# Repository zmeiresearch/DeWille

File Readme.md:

# DeWille - A modular Audio DAC platform

DeWille is designed to be a set of building blocks for audio DACs. Currently, the following 'blocks' are planned:
* A Base board - Power supplies, interconnects, physical board support
* A Control board - Input selection, reclocking, other digital signal processing
* A PCM1792 DAC board
* An I/V converter board

## Features:
### Inputs/Outputs and interface
* Supports multiple input and output formats:
  * I2S, Left-justified and right-justified PCM
  * S/PDIF, optical and coaxial
  * (Maybe) DSD
* Supports at least 24-bit@192kHz
* Configurable asynchronous reclocking with a FIFO
* Provision for USB support based on either XMOS or Amanero COTS board 
* Provision for Bluetooth audio support
* Provision for playback via WiFi
* Provision for an (oled?) display

### Analog side
* DAC section based on PCM1792
* Supports DAC Mono mode
* Supports PCM1792(4) in NOS mode (inspired by DDAC)
* CCS for PCM1792 Iref
* Supports multiple I/V Converters
* Low-noise power supply for both analog and digital sections

## Design considerations

### Control board
The control board is by far the most complex one in the set. It implements input selection, reclocking as well as all
the signal conversion and processing required to drive the DACs. Several distinct components work together to do this 
- an FPGA, a clock generator block and an MCU module. All the blocks are connected to each other via an SPI bus, with 
the MCU acting as master. The SPI bus also connects to the two DAC boards, allowing on-the-fly reconfiguration as 
required.

#### Hardware Design
* **FPGA**
The FPGA is the one actually doing all the signal manipulation and transformation work. It takes I2S data (PCM and DSD
planned for the future), does the actual reclocking (if told to do so) and outputs I2S (DSD planned for the future) to
the two separate DAC board.

The choice of an FPGA has been a difficult one. First and foremost, an SMD(QFP) package is a must. I have no problem
hand-soldering 0402 components, but I have neither the equipment nor the expertise to handle BGAs reliably. This 
alone limits the choice to basically Xilinx Spartan 3 and some Lattice families. (Intel and Microchip not considered
for different reasons). With ISE 14.7 the last one supporting Spartan 3 and the family NRND for new designs in general
I settled on Lattice, LFXP2-8E-5TN144 in particular. MachXO2 is also an option for a future redesign.

There is an on-board 8-bit wide SRAM chip, with a maximal capacity of 8MBit. Possiblity for a future update is either 
increasing the SRAM size (larger buffer) or increasing the datapath width (better throughput/lower latency).

The FPGA can also be programmed and debugged using the integrated FT2232 interface or the standard Lattice JTAG
connector. If using the FT2232, the second channel is connected to two FPGA pins that could implement a debug UART.

* **Clock generator**
The clock generator block is implemented with two oscillators (at 24.576MHz and 22.5792MHz) and an Si5344 multiplexer,
jitter reduction and clock output buffer circuit. Two of the clock outputs go directly to the DAC boards via either 
the pin header or a dedicated SMA interconnect, while the third is distributed to the FPGA to drive the reclocking 
internally. This clock arrangement is guaranteed to introduce a phase margin between the master clock and the bit/data
clock, but the PCM1794(2) and, in theory, all other DACs that require a System/Master clock do not need a specific 
relation between the two, as long as it remains a fixed one.
Regular oscillators are used rather than TCXOs because the actual frequency and long term drift are not that important 
to the sound quality and the Si5344 performance dominates the short-term jitter performance 

Possibility for a future enchancement is to also route the SCK input from the two I2S inputs to the remaining two
Si5344 inputs to allow source-synchronous operation as well.

* **MCU**
A ESP32-DevKit module was selected for the main MCU. The rationale to use an off-the-shelf MCU module is two-fold.
_First,_ by using an COTS hardware module with a well-established and easy to use software ecosystem behind it, I'll
be able to focus on the signal processing part of the project.
_Second,_ it will be much easier to implement other functionality in the future - OTA updates, including the FPGA 
bitstream, WiFi streaming, Alexa/Google home integration, etc.

* **Power Supply**
The control board takes a single, 5V regulated power supply. There is an on-board protection by means of a polyfuse
and a 6.8V Transil. This is powering a total of 6 voltage regulators:
  * +3V3_IO and +3V3_FPGA -  used for FPGA I/O ports, Debug/Program USB and on-board LEDs
  * +1V2_FPGA - FPGA Core supply
  * +3V3_CLKOUT - Clock outputs of Si5344
  * +3V3_VDDACLK and +1V8VDDCLK - analog and digital sections of Si5344 respectively
  * +3v3_VDDOSC - the two crystal oscillators
  * The on-module voltage regulator in the ESP32 module.

### DAC PCM1794(2)

### Base Board
The base board is responsible for physically carying the different modules together, connecting them electrically and
providing all the required power supplies. In addition, it implements input signal galvanic isolation to limit the harm
in case of failure of signal sources.

* **Power supply**
The base board takes a 220/110VAC mains supply and has two separate sets of transformers. Either 50VAC toroidal power
transformers or PCB-mounted sealed ones can be used. One of the transformers is providing the +5V regulated supply
necessary for the digital part of the schematic, while the other provides a +/- 15V supply.

All three +5V power supplies are filtered and regulated using a hybrid capacitance multiplier/regulator circut. In
addition, there are also two 3.3V regulators for the input galvanic isolators - an LDO for the 'in' side and a 
DC-DC for the 'out' side.

### I to V module
**WiP/TBD.** Assumed to have the same dimensions as the DAC module while creating the Base board.

## FAQ
* **Is DeWille HiFi/Audiophile grade?**
  No. It will just sound good.
* **Where does the name DeWille come from?**
  It was inspired by a [Frey Wille](https://www.freywille.com) scharf that happened to be around while thinking about
  a name for the project.

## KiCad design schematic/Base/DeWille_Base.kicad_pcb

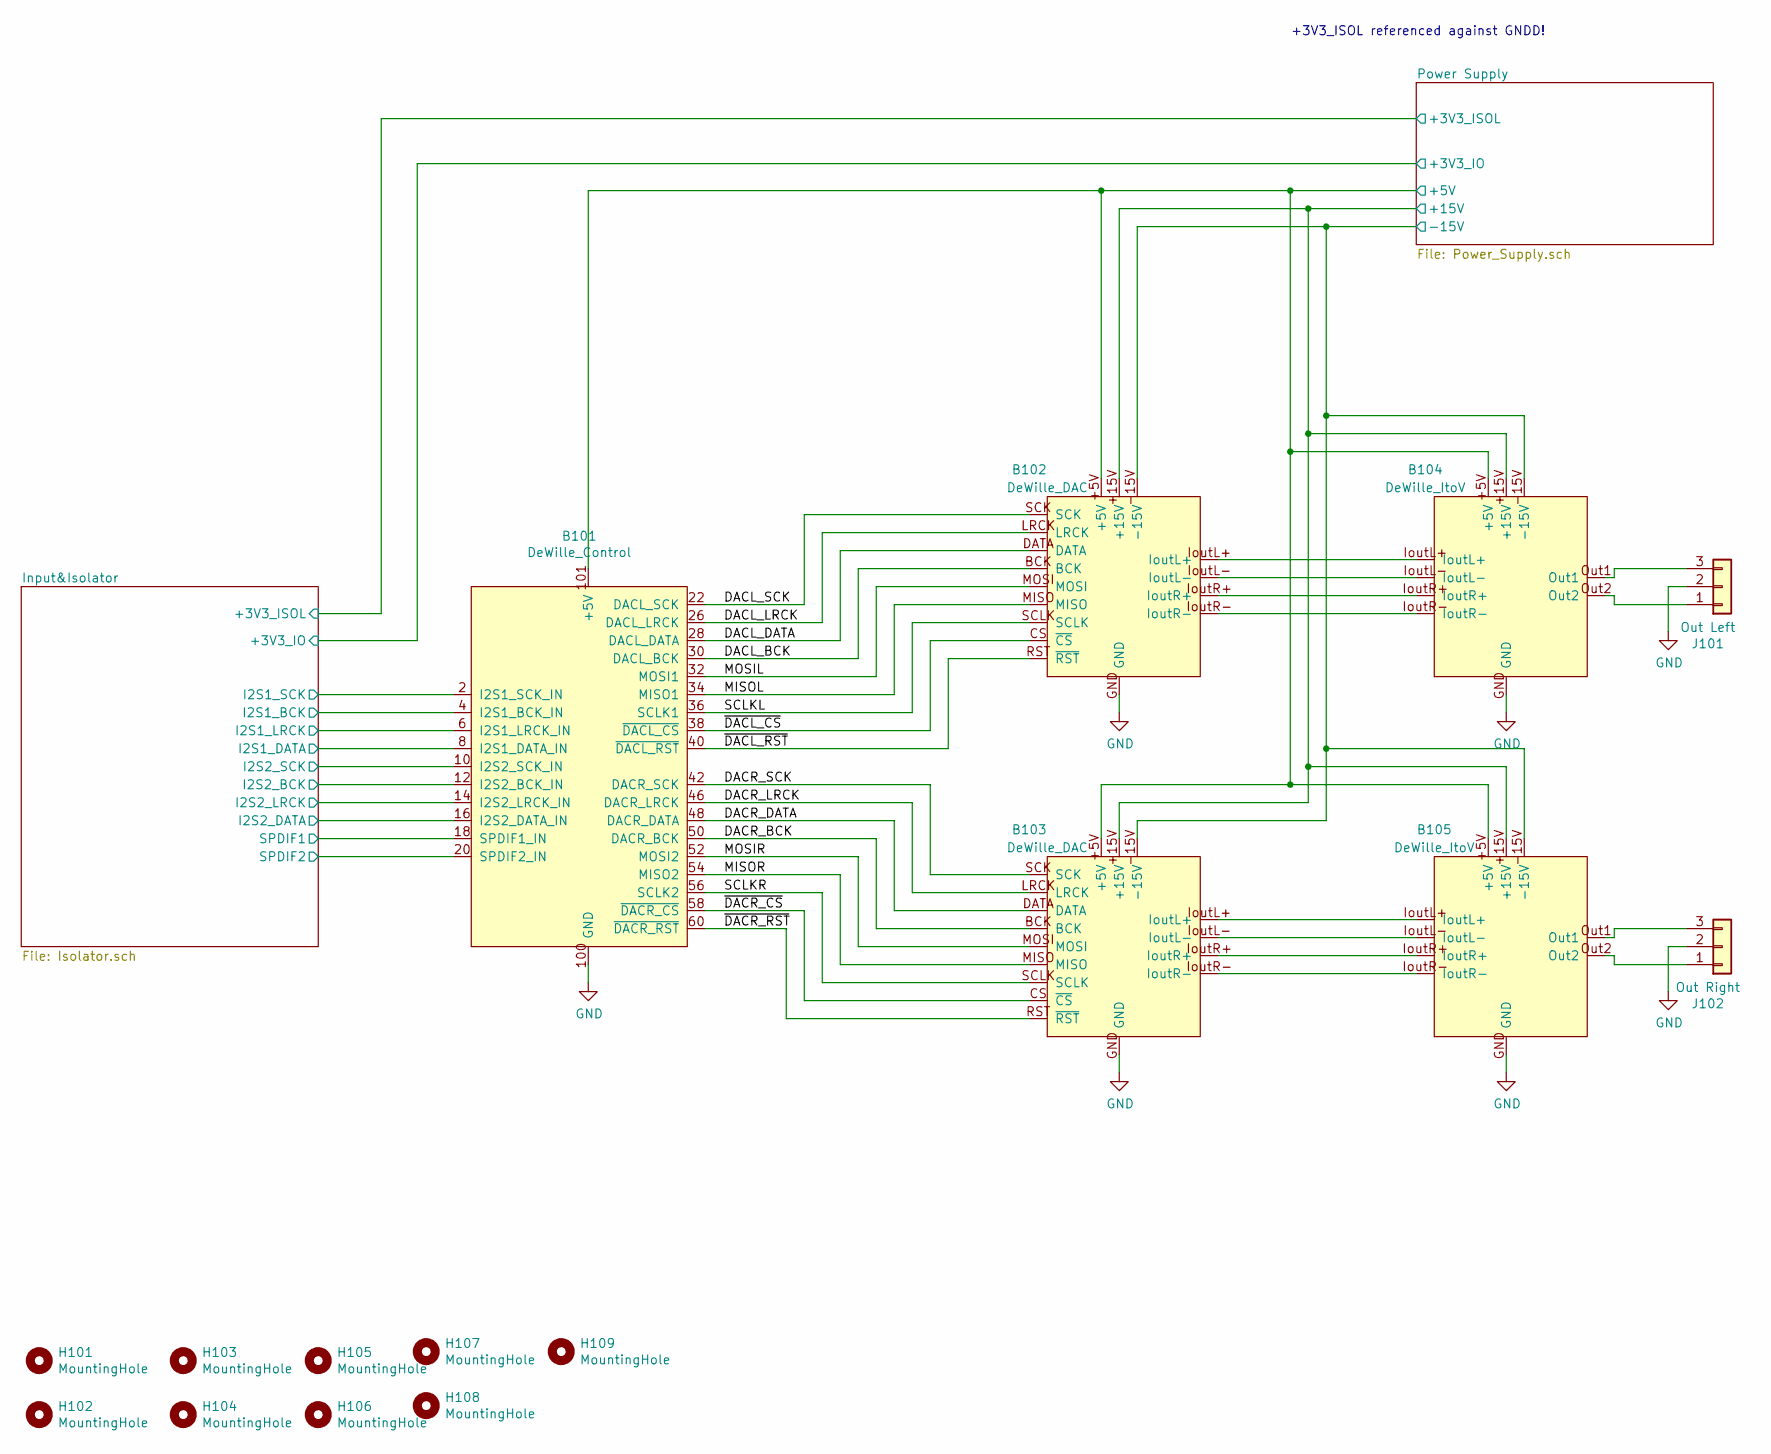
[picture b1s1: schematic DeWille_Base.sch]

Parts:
B101: DeWille_Control
B102, B103: DeWille_DAC
B104, B105: DeWille_ItoV
H101, H102, H103, H104, H105, H106, H107, H108, H109: MountingHole; MountingHole_3.2mm_M3_Pad
J101: Out Left; TerminalBlock_Dinkle_DT-55-B01X-03_P10.00mm
J102: Out Right; TerminalBlock_Dinkle_DT-55-B01X-03_P10.00mm

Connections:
/DACL_BCK: B101.30 (DACL_BCK), B102.BCK
/DACL_DATA: B101.28 (DACL_DATA), B102.DATA
/DACL_LRCK: B101.26 (DACL_LRCK), B102.LRCK
/DACL_SCK: B101.22 (DACL_SCK), B102.SCK
/DACR_BCK: B101.50 (DACR_BCK), B103.BCK
/DACR_DATA: B101.48 (DACR_DATA), B103.DATA
/DACR_LRCK: B101.46 (DACR_LRCK), B103.LRCK
/DACR_SCK: B101.42 (DACR_SCK), B103.SCK
/Input&Isolator/I2S1_BCK: B101.4 (I2S1_BCK_IN); also elsewhere on the board
/Input&Isolator/I2S1_DATA: B101.8 (I2S1_DATA_IN); also elsewhere on the board
/Input&Isolator/I2S1_LRCK: B101.6 (I2S1_LRCK_IN); also elsewhere on the board
/Input&Isolator/I2S1_SCK: B101.2 (I2S1_SCK_IN); also elsewhere on the board
/Input&Isolator/I2S2_BCK: B101.12 (I2S2_BCK_IN); also elsewhere on the board
/Input&Isolator/I2S2_DATA: B101.16 (I2S2_DATA_IN); also elsewhere on the board
/Input&Isolator/I2S2_LRCK: B101.14 (I2S2_LRCK_IN); also elsewhere on the board
/Input&Isolator/I2S2_SCK: B101.10 (I2S2_SCK_IN); also elsewhere on the board
/Input&Isolator/SPDIF1: B101.18 (SPDIF1_IN); also elsewhere on the board
/Input&Isolator/SPDIF2: B101.20 (SPDIF2_IN); also elsewhere on the board
/MISOL: B101.34 (MISO1), B102.MISO
/MISOR: B101.54 (MISO2), B103.MISO
/MOSIL: B101.32 (MOSI1), B102.MOSI
/MOSIR: B101.52 (MOSI2), B103.MOSI
/Power Supply/+5V: B101.101 (+5V), B102.+5V, B103.+5V, B104.+5V, B105.+5V; also elsewhere on the board
/Power Supply/+15V: B102.+15V, B103.+15V, B104.+15V, B105.+15V; also elsewhere on the board
/Power Supply/-15V: B102.-15V, B103.-15V, B104.-15V, B105.-15V; also elsewhere on the board
/SCLKL: B101.36 (SCLK1), B102.SCLK
/SCLKR: B101.56 (SCLK2), B103.SCLK
/~DACL_CS~: B101.38 (~DACL_CS~), B102.~CS~
/~DACL_RST~: B101.40 (~DACL_RST~), B102.~RST~
/~DACR_CS~: B101.58 (~DACR_CS~), B103.~CS~
/~DACR_RST~: B101.60 (~DACR_RST~), B103.~RST~
GND: B101.100 (GND), B102.GND, B103.GND, B104.GND, B105.GND, J101.2, J102.2; also elsewhere on the board
unnamed: B102.IoutL+, B104.IoutL+
unnamed: B102.IoutL-, B104.IoutL-
unnamed: B102.IoutR+, B104.IoutR+
unnamed: B102.IoutR-, B104.IoutR-
unnamed: B103.IoutL+, B105.IoutL+
unnamed: B103.IoutL-, B105.IoutL-
unnamed: B103.IoutR+, B105.IoutR+
unnamed: B103.IoutR-, B105.IoutR-
unnamed: B104.Out1, J101.3
unnamed: B104.Out2, J101.1
unnamed: B105.Out1, J102.3
unnamed: B105.Out2, J102.1

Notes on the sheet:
+3V3_ISOL referenced against GNDD!

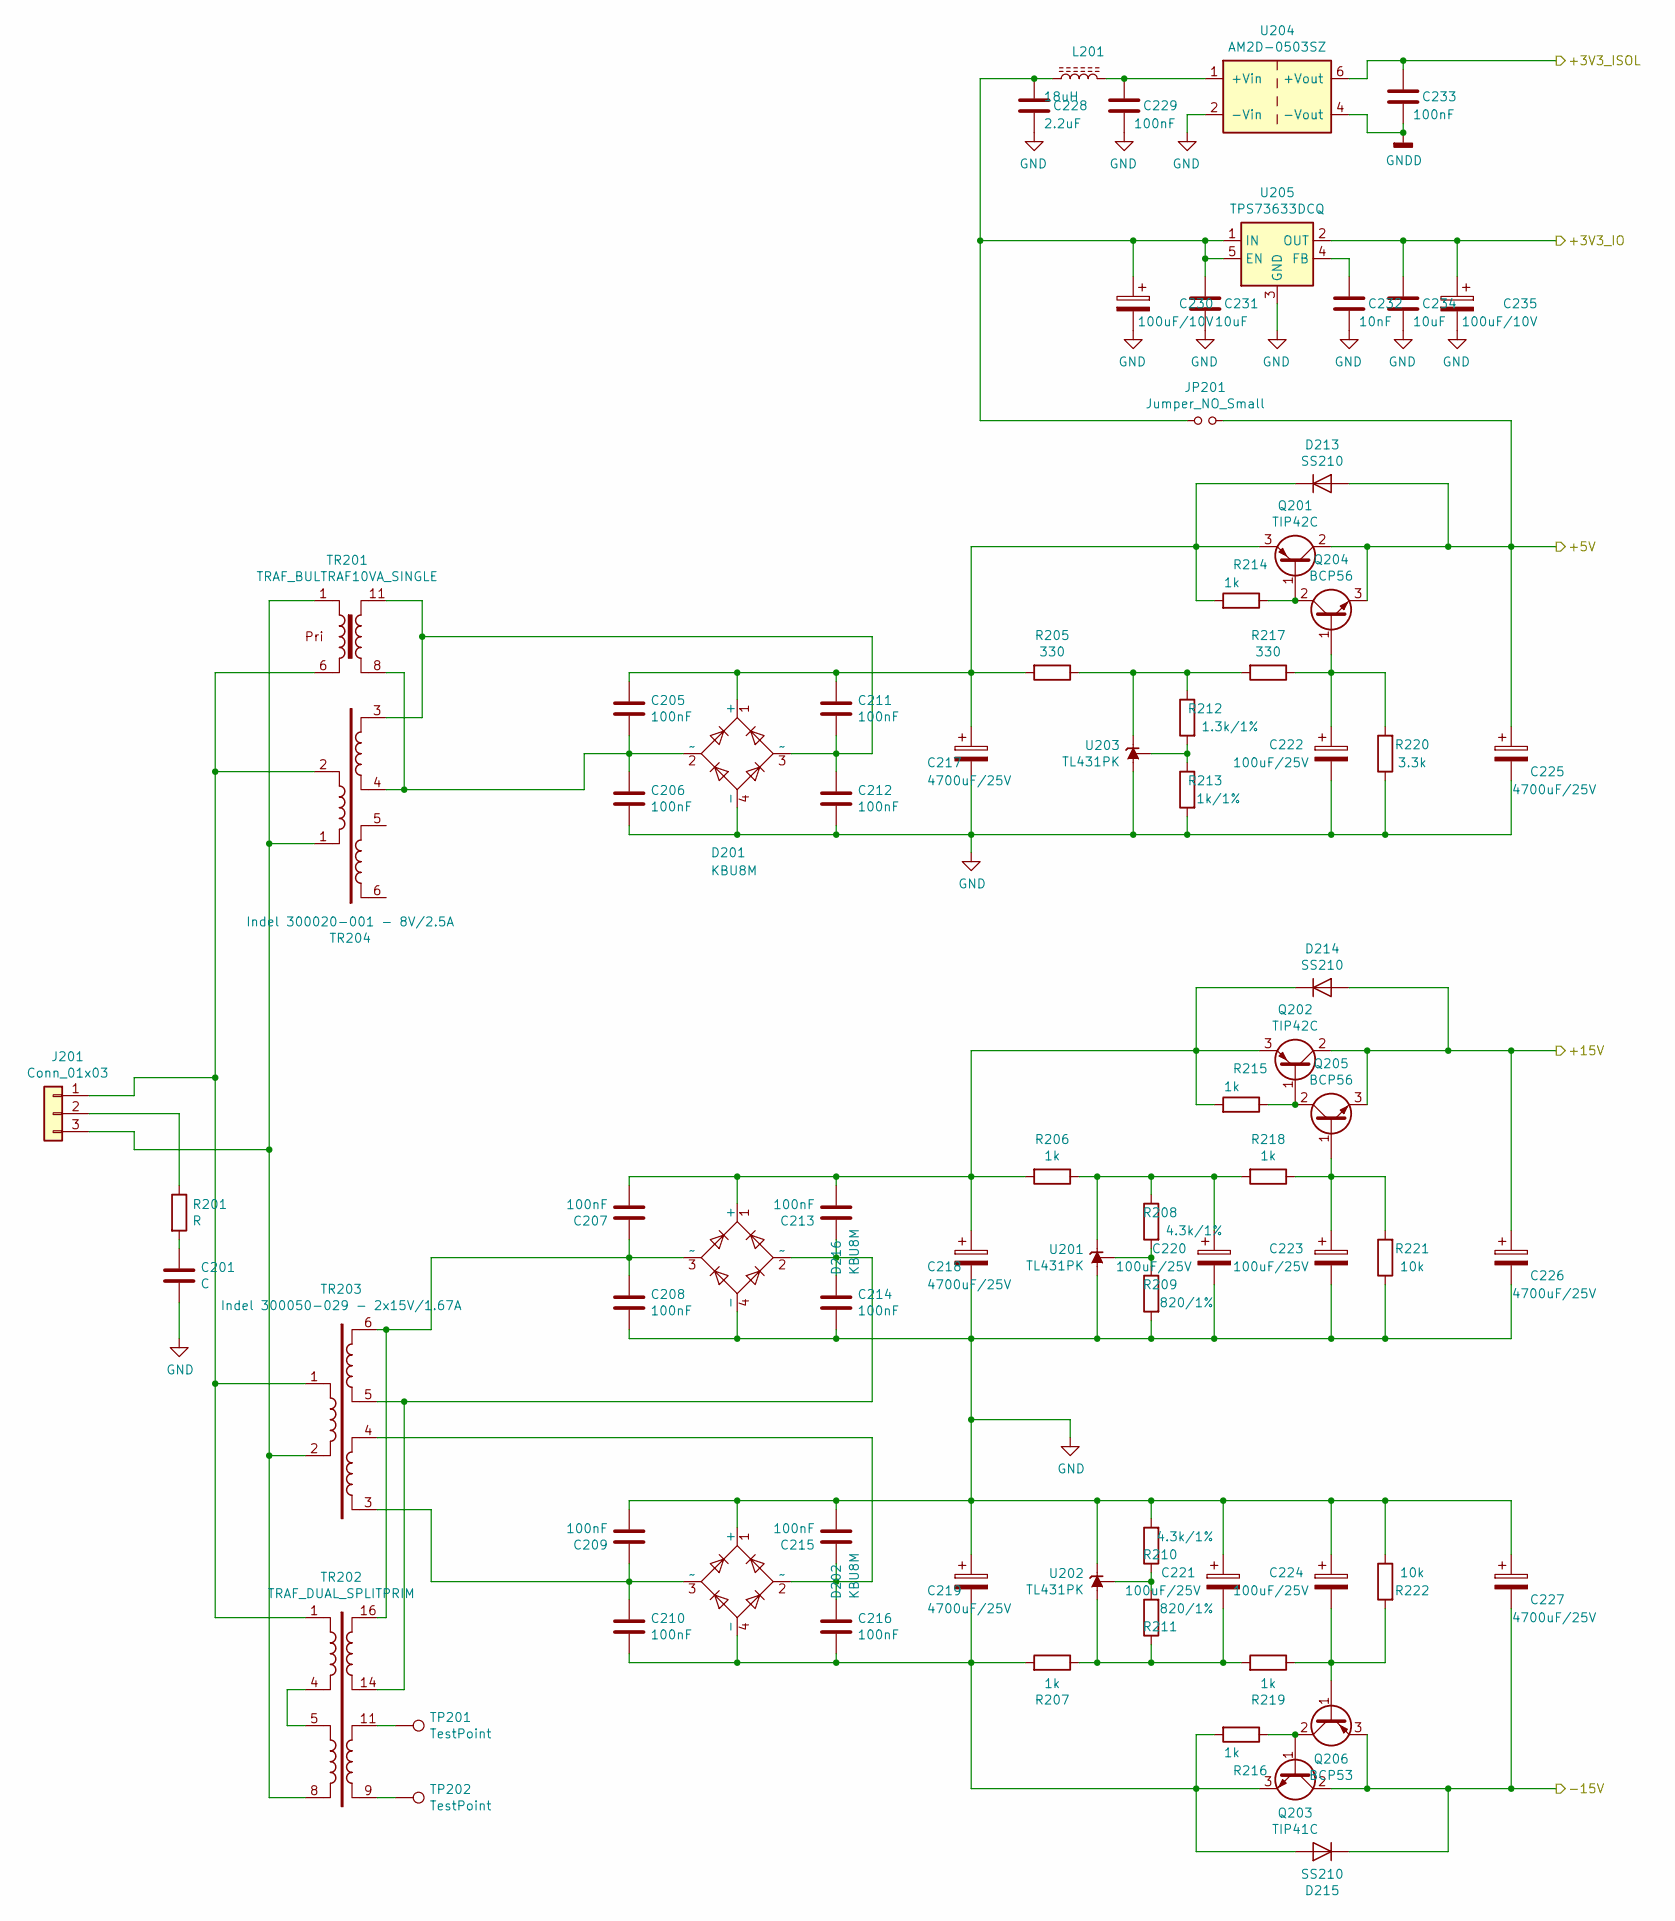
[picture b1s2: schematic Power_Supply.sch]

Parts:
C201: C; C_Rect_L13.0mm_W6.0mm_P10.00mm_FKS3_FKP3_MKS4
C205, C206, C207, C208, C209, C210, C211, C212, C213, C214, C215, C216: 100nF; C_Rect_L7.2mm_W3.0mm_P5.00mm_FKS2_FKP2_MKS2_MKP2
C217, C218, C219, C225, C226, C227: 4700uF/25V; CP_Radial_D18.0mm_P7.50mm
C220, C221, C222, C223, C224: 100uF/25V; CP_Radial_D8.0mm_P3.50mm
C228: 2.2uF; C_0603_1608Metric
C229, C233: 100nF; C_0603_1608Metric
C230, C235: 100uF/10V; C_Elec_6.3x5.4
C231, C234: 10uF; C_0603_1608Metric
C232: 10nF; C_0603_1608Metric
D201, D202, D216: KBU8M; Diode_Bridge_Vishay_KBU
D213, D214, D215: SS210; D_SMB
J201: Conn_01x03; TerminalBlock_Dinkle_DT-55-B01X-03_P10.00mm
JP201: Jumper_NO_Small; PinSocket_1x02_P2.54mm_Vertical
L201: 18uH; L_Radial_D7.5mm_P3.50mm_Fastron_07P
Q201, Q202: TIP42C; TO-220-3_Vertical
Q203: TIP41C; TO-220-3_Vertical
Q204, Q205: BCP56; SOT-223
Q206: BCP53; SOT-223
R201: R; R_Axial_DIN0207_L6.3mm_D2.5mm_P10.16mm_Horizontal
R205, R217: 330; R_1206_3216Metric
R206, R207, R214, R215, R216, R218, R219: 1k; R_0603_1608Metric
R208, R210: 4.3k/1%; R_0603_1608Metric
R209, R211: 820/1%; R_0603_1608Metric
R212: 1.3k/1%; R_0603_1608Metric
R213: 1k/1%; R_0603_1608Metric
R220: 3.3k; R_1206_3216Metric
R221, R222: 10k; R_0603_1608Metric
TP201, TP202: TestPoint; TestPoint_THTPad_D2.0mm_Drill1.0mm
TR201: TRAF_BULTRAF10VA_SINGLE; TRAF_BULTRAF10VA
TR202: TRAF_DUAL_SPLITPRIM; TRAF_ANG_DUAL_18_24VA
TR203: Indel 300050-029 - 2x15V/1.67A; TRAF_TOROID_50VA
TR204: Indel 300020-001 - 8V/2.5A; TRAF_TOROID_50VA
U201, U202, U203: TL431PK; SOT-89-3
U204: AM2D-0503SZ; Converter_DCDC_AM2D
U205: TPS73633DCQ; SOT-223-6_TabPin3

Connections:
/Input&Isolator/+3V3_IO: C234.2, C235.1, U205.2 (OUT); also elsewhere on the board
/Input&Isolator/+3V3_ISOL: C233.2, U204.6 (+Vout); also elsewhere on the board
/Power Supply/+5V: C225.1, D213.2 (A), JP201.2, Q201.2 (C), Q204.3 (E); also elsewhere on the board
/Power Supply/+15V: C226.1, D214.2 (A), Q202.2 (C), Q205.3 (E); also elsewhere on the board
/Power Supply/-15V: C227.2, D215.1 (K), Q203.2 (C), Q206.3 (E); also elsewhere on the board
GND: C201.2, C206.2, C208.2, C209.2, C212.2, C214.2, C215.2, C217.2, C218.2, C219.1, C220.2, C221.1, C222.2, C223.2, C224.1, C225.2, C226.2, C227.1, C228.1, C229.1, C230.2, C231.1, C232.1, C234.1, C235.2, D201.4 (-), D202.1 (+), D216.4 (-), R209.2, R210.2, R213.2, R220.1, R221.1, R222.1, U201.2 (A), U202.3 (K), U203.2 (A), U204.2 (-Vin), U205.3 (GND); also elsewhere on the board
GNDD: C233.1, U204.4 (-Vout); also elsewhere on the board
unnamed: C201.1, R201.2
unnamed: C205.1, C211.1, C217.1, D201.1 (+), D213.1 (K), Q201.3 (E), R205.2, R214.2
unnamed: C205.2, C206.1, D201.2 (~~), TR201.8, TR204.4
unnamed: C207.1, C208.1, D216.3 (~~), TR202.16, TR203.6
unnamed: C207.2, C213.2, C218.1, D214.1 (K), D216.1 (+), Q202.3 (E), R206.2, R215.2
unnamed: C209.1, C210.1, D202.3 (~~), TR203.3
unnamed: C210.2, C216.2, C219.2, D202.4 (-), D215.2 (A), Q203.3 (E), R207.2, R216.2
unnamed: C211.2, C212.1, D201.3 (~~), TR201.11, TR204.3
unnamed: C213.1, C214.1, D216.2 (~~), TR202.14, TR203.5
unnamed: C215.1, C216.1, D202.2 (~~), TR203.4
unnamed: C220.1, R206.1, R208.1, R218.2, U201.3 (K)
unnamed: C221.2, R207.1, R211.1, R219.2, U202.2 (A)
unnamed: C222.1, Q204.1 (B), R217.1, R220.2
unnamed: C223.1, Q205.1 (B), R218.1, R221.2
unnamed: C224.2, Q206.1 (B), R219.1, R222.2
unnamed: C228.2, C230.1, C231.2, JP201.1, L201.2, U205.1 (IN), U205.5 (EN)
unnamed: C229.2, L201.1, U204.1 (+Vin)
unnamed: C232.2, U205.4 (FB)
unnamed: J201.1, TR201.6, TR202.1, TR203.1, TR204.2
unnamed: J201.2, R201.1
unnamed: J201.3, TR201.1, TR202.8, TR203.2, TR204.1
unnamed: Q201.1 (B), Q204.2 (C), Q204.4 (C), R214.1
unnamed: Q202.1 (B), Q205.2 (C), Q205.4 (C), R215.1
unnamed: Q203.1 (B), Q206.2 (C), Q206.4 (C), R216.1
unnamed: R205.1, R212.1, R217.2, U203.3 (K)
unnamed: R208.2, R209.1, U201.1 (REF)
unnamed: R210.1, R211.2, U202.1 (REF)
unnamed: R212.2, R213.1, U203.1 (REF)
unnamed: TP201.1, TR202.11
unnamed: TP202.1, TR202.9
unnamed: TR202.4, TR202.5

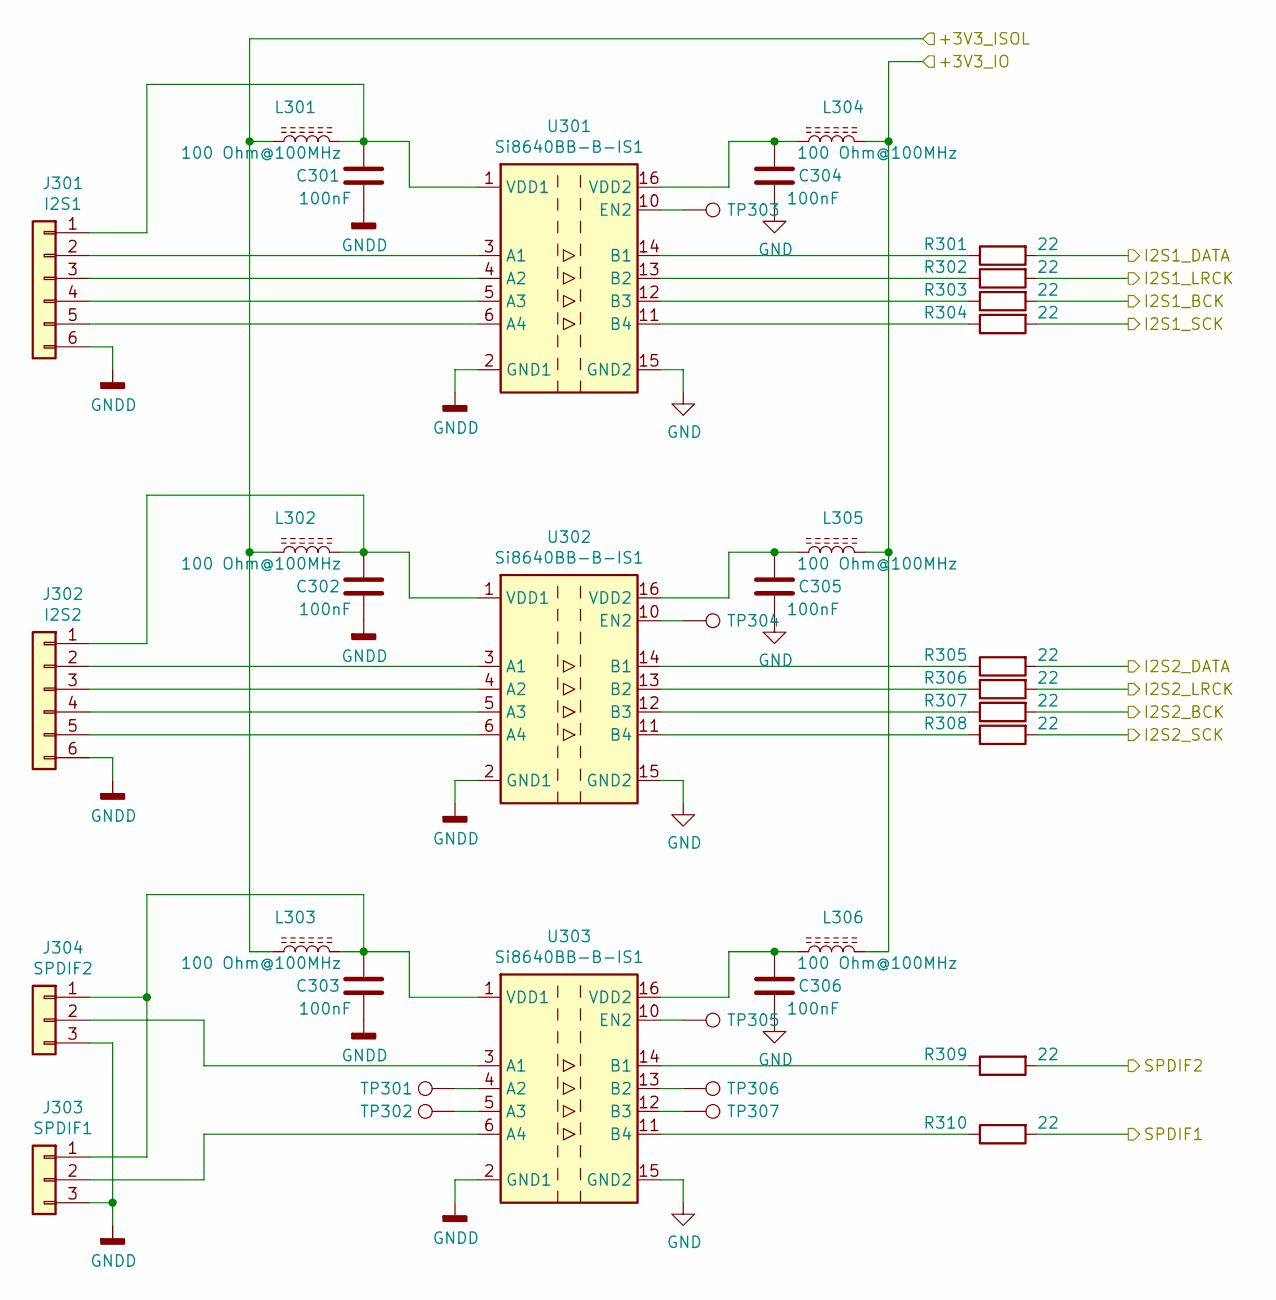
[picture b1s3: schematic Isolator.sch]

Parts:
C301, C302, C303, C304, C305, C306: 100nF; C_0603_1608Metric
J301: I2S1; PinSocket_1x06_P2.54mm_Vertical
J302: I2S2; PinSocket_1x06_P2.54mm_Vertical
J303: SPDIF1; PinSocket_1x03_P2.54mm_Vertical
J304: SPDIF2; PinSocket_1x03_P2.54mm_Vertical
L301, L302, L303, L304, L305, L306: 100 Ohm@100MHz; L_0805_2012Metric
R301, R302, R303, R304, R305, R306, R307, R308, R309, R310: 22; R_0603_1608Metric
TP301, TP302, TP303, TP304, TP305, TP306, TP307: TestPoint; TestPoint_Pad_D1.0mm
U301, U302, U303: Si8640BB-B-IS1; SOIC-16_3.9x9.9mm_P1.27mm

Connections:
/Input&Isolator/+3V3_IO: L304.1, L305.1, L306.1; also elsewhere on the board
/Input&Isolator/+3V3_ISOL: L301.1, L302.1, L303.1; also elsewhere on the board
/Input&Isolator/I2S1_BCK: R303.2; also elsewhere on the board
/Input&Isolator/I2S1_DATA: R301.2; also elsewhere on the board
/Input&Isolator/I2S1_LRCK: R302.2; also elsewhere on the board
/Input&Isolator/I2S1_SCK: R304.2; also elsewhere on the board
/Input&Isolator/I2S2_BCK: R307.2; also elsewhere on the board
/Input&Isolator/I2S2_DATA: R305.2; also elsewhere on the board
/Input&Isolator/I2S2_LRCK: R306.2; also elsewhere on the board
/Input&Isolator/I2S2_SCK: R308.2; also elsewhere on the board
/Input&Isolator/SPDIF1: R310.2; also elsewhere on the board
/Input&Isolator/SPDIF2: R309.2; also elsewhere on the board
GND: C304.1, C305.1, C306.1, U301.9 (GND2), U301.15 (GND2), U302.9 (GND2), U302.15 (GND2), U303.9 (GND2), U303.15 (GND2); also elsewhere on the board
GNDD: C301.1, C302.1, C303.1, J301.6, J302.6, J303.3, J304.3, U301.2 (GND1), U301.8 (GND1), U302.2 (GND1), U302.8 (GND1), U303.2 (GND1), U303.8 (GND1); also elsewhere on the board
unnamed: C301.2, J301.1, L301.2, U301.1 (VDD1)
unnamed: C302.2, J302.1, L302.2, U302.1 (VDD1)
unnamed: C303.2, J303.1, J304.1, L303.2, U303.1 (VDD1)
unnamed: C304.2, L304.2, U301.16 (VDD2)
unnamed: C305.2, L305.2, U302.16 (VDD2)
unnamed: C306.2, L306.2, U303.16 (VDD2)
unnamed: J301.2, U301.3 (A1)
unnamed: J301.3, U301.4 (A2)
unnamed: J301.4, U301.5 (A3)
unnamed: J301.5, U301.6 (A4)
unnamed: J302.2, U302.3 (A1)
unnamed: J302.3, U302.4 (A2)
unnamed: J302.4, U302.5 (A3)
unnamed: J302.5, U302.6 (A4)
unnamed: J303.2, U303.6 (A4)
unnamed: J304.2, U303.3 (A1)
unnamed: R301.1, U301.14 (B1)
unnamed: R302.1, U301.13 (B2)
unnamed: R303.1, U301.12 (B3)
unnamed: R304.1, U301.11 (B4)
unnamed: R305.1, U302.14 (B1)
unnamed: R306.1, U302.13 (B2)
unnamed: R307.1, U302.12 (B3)
unnamed: R308.1, U302.11 (B4)
unnamed: R309.1, U303.14 (B1)
unnamed: R310.1, U303.11 (B4)
unnamed: TP301.1, U303.4 (A2)
unnamed: TP302.1, U303.5 (A3)
unnamed: TP303.1, U301.10 (EN2)
unnamed: TP304.1, U302.10 (EN2)
unnamed: TP305.1, U303.10 (EN2)
unnamed: TP306.1, U303.13 (B2)
unnamed: TP307.1, U303.12 (B3)

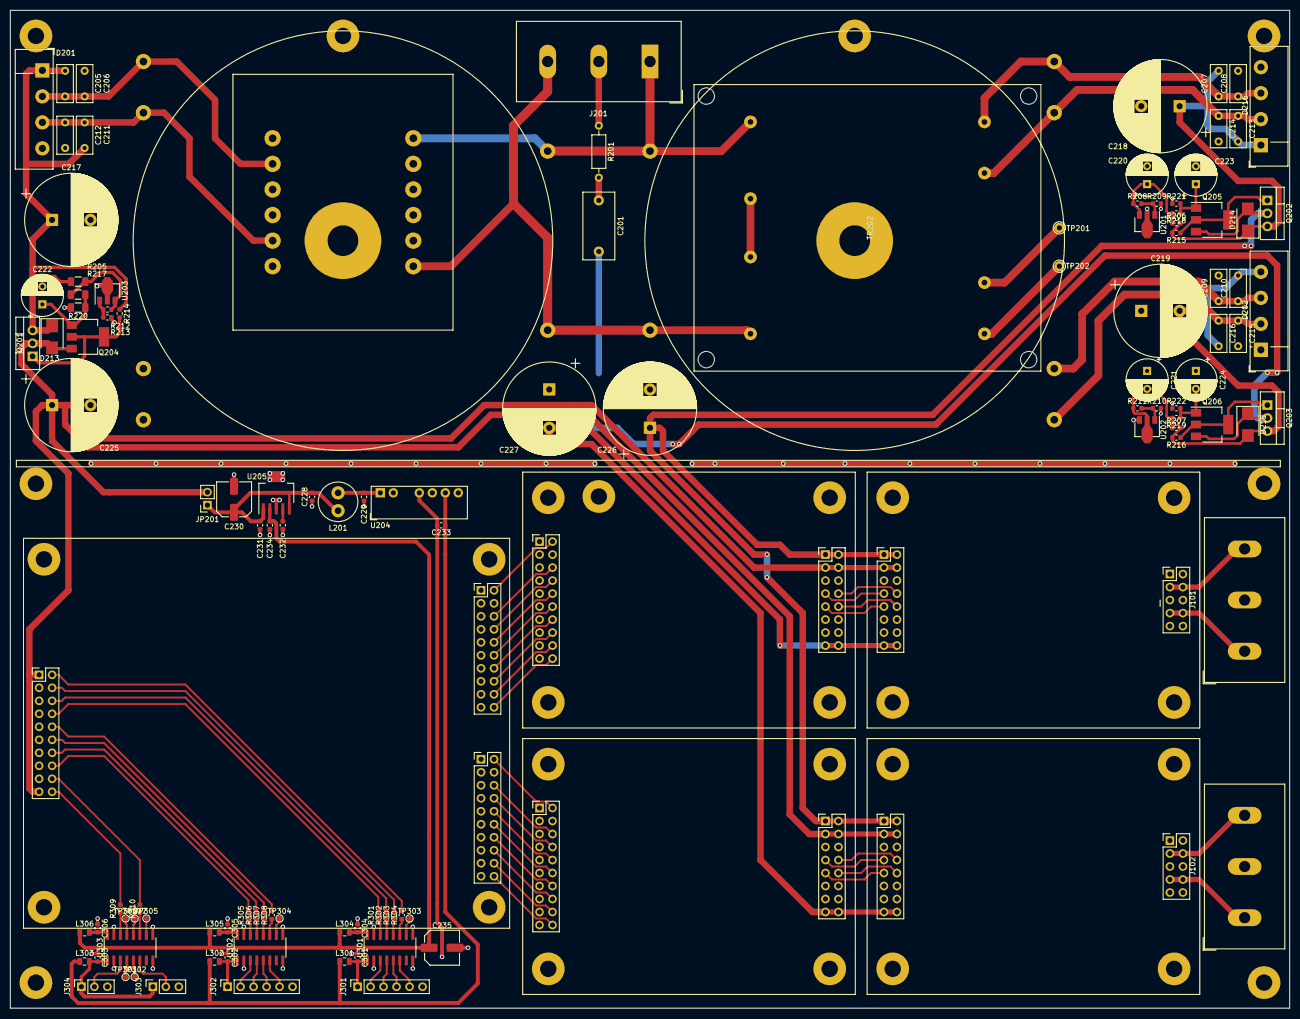
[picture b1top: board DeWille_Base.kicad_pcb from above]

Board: 2 copper layers, 250.0 x 195.0 mm, 129 parts (0 on the bottom side), 111 nets.

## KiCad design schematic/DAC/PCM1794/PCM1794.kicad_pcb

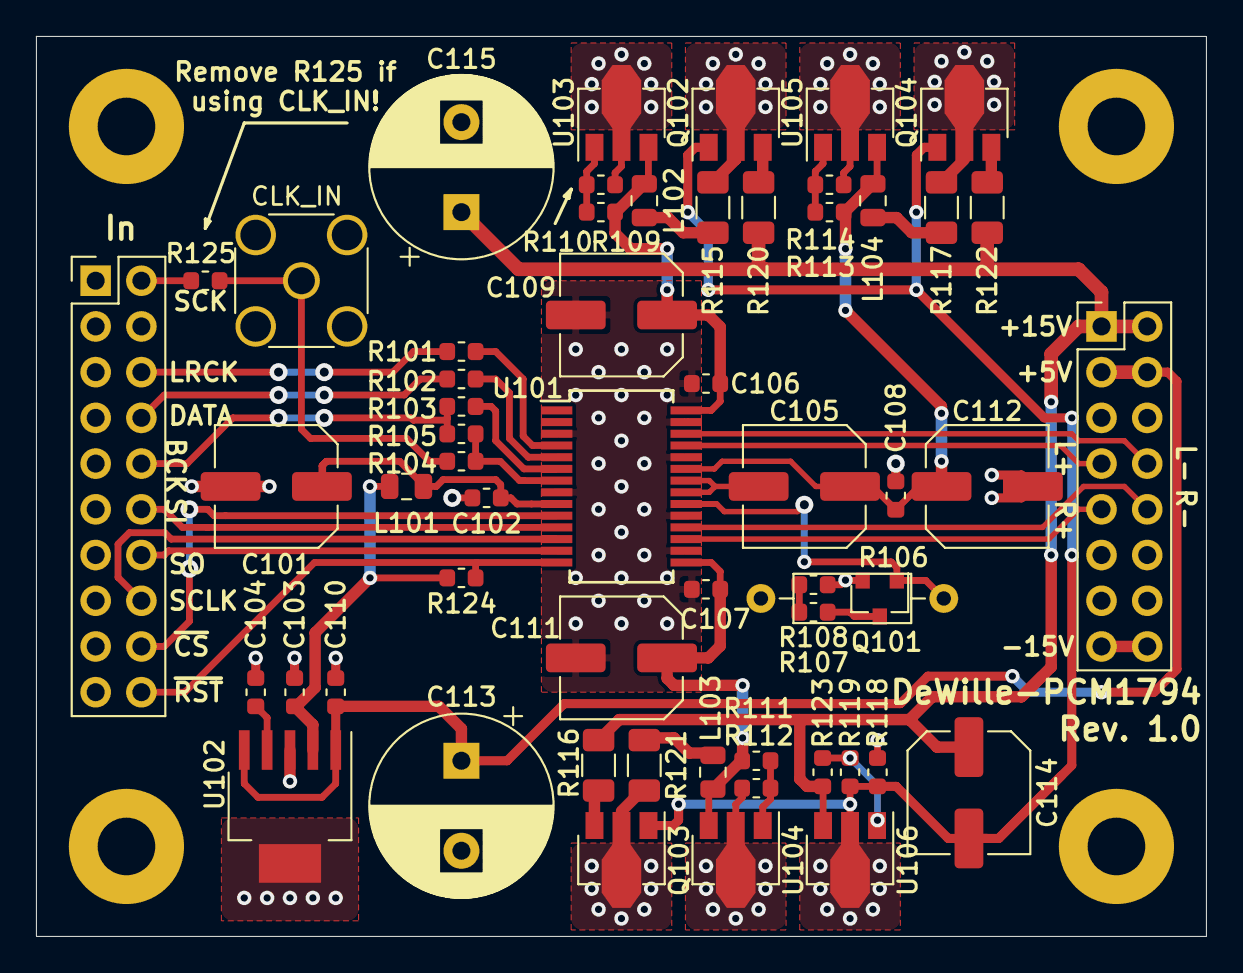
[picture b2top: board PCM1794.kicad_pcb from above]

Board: 2 copper layers, 65.0 x 50.0 mm, 62 parts (1 on the bottom side), 46 nets.

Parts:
C101, C105, C109, C111, C112, C114: 100uF/10V; C_Elec_6.3x7.7
C102, C106, C107, C108: 100nF; C_0603_1608Metric
C103, C110: 10uF; C_0603_1608Metric
C104: 10nF; C_0603_1608Metric
C113, C115: 1000uF/16V; CP_Radial_D10.0mm_P5.00mm
H101, H102, H103, H104: MountingHole; MountingHole_3.2mm_M3_Pad
J101: In; PinHeader_2x10_P2.54mm_Vertical
J102: Out; PinHeader_2x08_P2.54mm_Vertical
J103: SMA F ST PCB; SMA_Amphenol_132134_Vertical
L101: 10 Ohm@100MHz; L_0805_2012Metric
L102, L103, L104: 100 Ohm@100MHz; L_0805_2012Metric
Q101: 2SK208; SOT-23
Q102, Q103, Q104: BCX53-16; SOT-89-3
R101, R102, R103, R104, R108, R125: 0; R_0603_1608Metric
R105: DNP; R_0603_1608Metric
R106: DNP/6K; R_Axial_DIN0207_L6.3mm_D2.5mm_P10.16mm_Horizontal
R107: 470; R_0603_1608Metric
R109, R110, R111, R112, R113, R114, R119, R123: 1k/1%; R_0603_1608Metric
R115, R116, R117: 100; R_1206_3216Metric
R118: 4.7k; R_0603_1608Metric
R120, R121, R122: 150; R_1206_3216Metric
R124: 10k; R_0603_1608Metric
U101: PCM1792A; SSOP-28_5.3x10.2mm_P0.65mm
U102: TPS73633DCQ; SOT-223-6_TabPin3
U103, U104, U105, U106: TL431PK; SOT-89-3
U107: Logo; Zmei-logo-small-inverted_silk

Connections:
/+5V: C110.2, C113.1, J102.3, J102.4, U102.1, U102.5
/+15VA: C114.1, C115.1, J102.1, J102.2, R120.1, R121.1, R122.1, R123.1, U106.3
/-15VA: J102.15, J102.16
/BCK: J101.10, R103.2, R105.2
/DATA: J101.8, R102.2
/IoutL+: J102.7, U101.25
/IoutL-: J102.8, U101.26
/IoutR+: J102.9, U101.17
/IoutR-: J102.10, U101.18
/LRCK: J101.6, R101.2
/MISO: J101.14, U101.13
/MOSI: J101.12, U101.11
/SCK: J103.1, R104.2, R125.1
/SCLK: J101.16, U101.12
/~CS~: J101.18, U101.10
/~RST~: J101.20, R124.1, U101.14
GND: C101.2, C102.2, C103.1, C104.1, C106.2, C107.2, C108.2, C109.2, C110.1, C111.2, C112.2, C113.2, C115.2, J101.1, J101.3, J101.4, J101.5, J101.7, J101.9, J101.11, J101.13, J101.15, J101.17, J101.19, J102.5, J102.6, J102.11, J102.12, J102.13, J102.14, J103.2, Q101.2, R106.2, R108.2, R110.2, R112.2, R114.2, R118.2, U101.3, U101.8, U101.16, U101.19, U101.24, U101.27, U102.3, U103.2, U104.2, U105.2
unnamed: C101.1, C102.1, L101.2, U101.9
unnamed: C103.2, L101.1, R124.2, U102.2
unnamed: C104.2, U102.4
unnamed: C105.1, C108.1, C112.1, L104.1, R113.1, U101.23, U105.3
unnamed: C105.2, U101.21, U101.22
unnamed: C106.1, C109.1, L102.1, R109.1, U101.28, U103.3
unnamed: C107.1, C111.1, L103.1, R111.1, U101.15, U104.3
unnamed: C114.2, Q102.1, Q103.1, Q104.1, R118.1, R119.2, U106.2
unnamed: J101.2, R125.2
unnamed: L102.2, R115.2
unnamed: L103.2, R116.2
unnamed: L104.2, R117.2
unnamed: Q101.1, R106.1, U101.20
unnamed: Q101.3, R107.1
unnamed: Q102.2, R115.1
unnamed: Q102.3, R120.2
unnamed: Q103.2, R116.1
unnamed: Q103.3, R121.2
unnamed: Q104.2, R117.1
unnamed: Q104.3, R122.2
unnamed: R101.1, U101.4
unnamed: R102.1, U101.5
unnamed: R103.1, U101.6
unnamed: R104.1, R105.1, U101.7
unnamed: R107.2, R108.1
unnamed: R109.2, R110.1, U103.1
unnamed: R111.2, R112.1, U104.1
unnamed: R113.2, R114.1, U105.1
unnamed: R119.1, R123.2, U106.1

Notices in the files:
schematic/Control/DeWille_Control.sch:
License: CC-Attribution-ShareAlike
